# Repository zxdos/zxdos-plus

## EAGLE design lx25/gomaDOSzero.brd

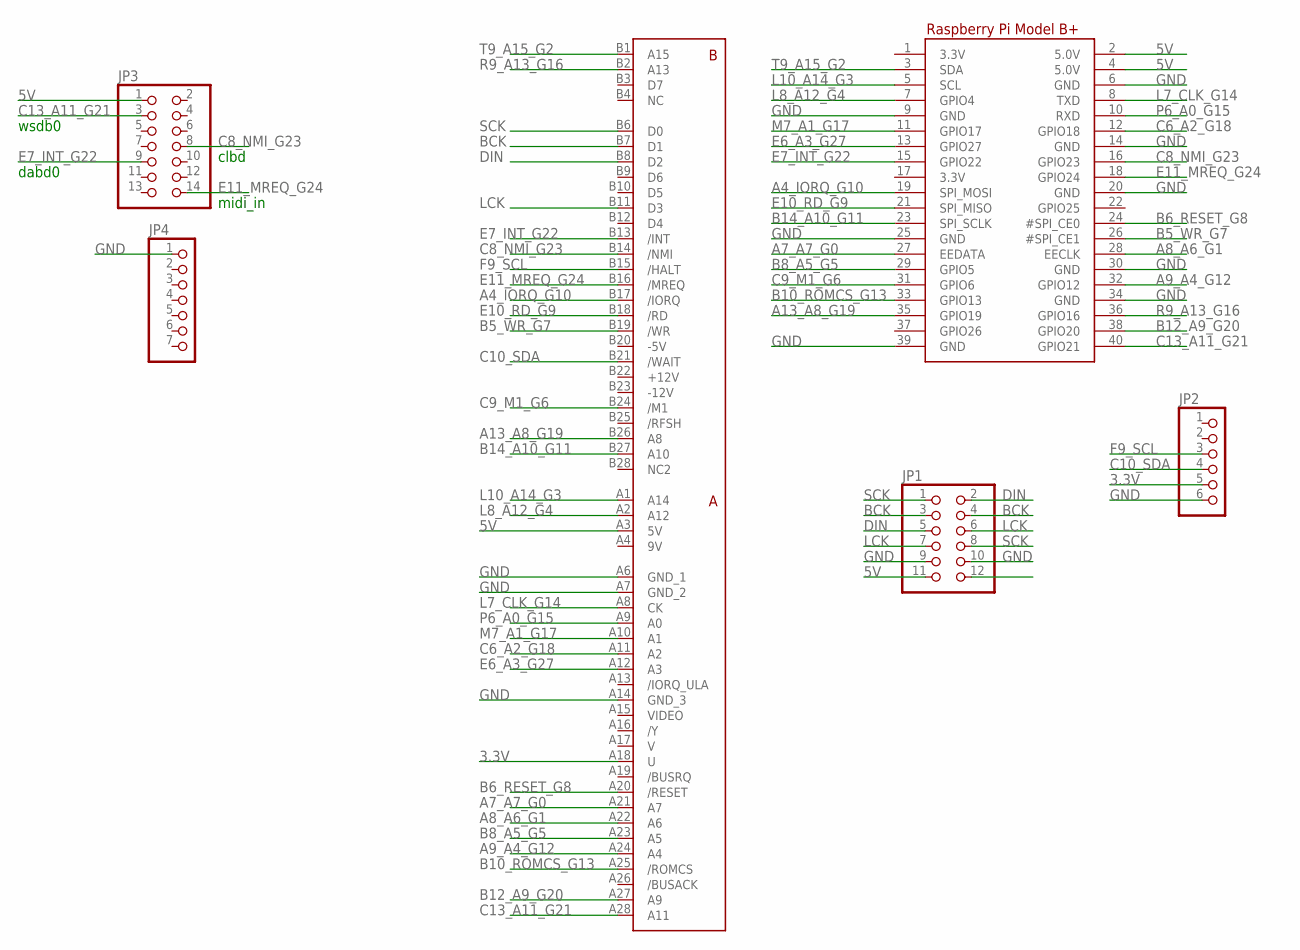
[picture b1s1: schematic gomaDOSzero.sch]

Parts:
JP1: PINHD-2X6; 2X06
JP2: PINHD-1X6/90; 1X06/90
JP3: PINHD-2X07_2.00; 2X07M
JP4: PINHD-1X07_2.00; 1X07M
RPI1: RASPBERRYPI_BPLUS_BONNETNODIM; PI_BONNET_NODIM
U$1: ZXSP_ED2X28_SPE_SOL_EDGE; 2X28_SPE2

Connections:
3.3V: JP2.5, U$1.A18 (U)
5V: JP1.11, JP1.12, JP3.1, RPI1.2 (5.0V), RPI1.4 (5.0V), U$1.A3 (5V)
9V: U$1.A4 (9V)
+12V: U$1.B22 (+12V)
-5V: U$1.B20 (-5V)
-12V: U$1.B23 (-12V)
A4_IORQ_G10: RPI1.19 (SPI_MOSI), U$1.B17 (/IORQ)
A7_A7_G0: RPI1.27 (EEDATA), U$1.A21 (A7)
A8_A6_G1: RPI1.28 (EECLK), U$1.A22 (A6)
A9_A4_G12: RPI1.32 (GPIO12), U$1.A24 (A4)
A13_A8_G19: RPI1.35 (GPIO19), U$1.B26 (A8)
B5_WR_G7: RPI1.26 (#SPI_CE1), U$1.B19 (/WR)
B6_RESET_G8: RPI1.24 (#SPI_CE0), U$1.A20 (/RESET)
B8_A5_G5: RPI1.29 (GPIO5), U$1.A23 (A5)
B10_ROMCS_G13: RPI1.33 (GPIO13), U$1.A25 (/ROMCS)
B12_A9_G20: RPI1.38 (GPIO20), U$1.A27 (A9)
B14_A10_G11: RPI1.23 (SPI_SCLK), U$1.B27 (A10)
BCK: JP1.3, JP1.4, U$1.B7 (D1)
C6_A2_G18: RPI1.12 (GPIO18), U$1.A11 (A2)
C8_NMI_G23: JP3.8, RPI1.16 (GPIO23), U$1.B14 (/NMI)
C9_M1_G6: RPI1.31 (GPIO6), U$1.B24 (/M1)
C10_SDA: JP2.4, U$1.B21 (/WAIT)
C13_A11_G21: JP3.3, RPI1.40 (GPIO21), U$1.A28 (A11)
DIN: JP1.2, JP1.5, U$1.B8 (D2)
E6_A3_G27: RPI1.13 (GPIO27), U$1.A12 (A3)
E7_INT_G22: JP3.9, RPI1.15 (GPIO22), U$1.B13 (/INT)
E10_RD_G9: RPI1.21 (SPI_MISO), U$1.B18 (/RD)
E11_MREQ_G24: JP3.14, RPI1.18 (GPIO24), U$1.B16 (/MREQ)
F9_SCL: JP2.3, U$1.B15 (/HALT)
GND: JP1.9, JP1.10, JP2.6, JP4.1, RPI1.6 (GND), RPI1.9 (GND), RPI1.14 (GND), RPI1.20 (GND), RPI1.25 (GND), RPI1.30 (GND), RPI1.34 (GND), RPI1.39 (GND), U$1.A6 (GND_1), U$1.A7 (GND_2), U$1.A14 (GND_3)
L7_CLK_G14: RPI1.8 (TXD), U$1.A8 (CK)
L8_A12_G4: RPI1.7 (GPIO4), U$1.A2 (A12)
L10_A14_G3: RPI1.5 (SCL), U$1.A1 (A14)
LCK: JP1.6, JP1.7, U$1.B11 (D3)
M7_A1_G17: RPI1.11 (GPIO17), U$1.A10 (A1)
P6_A0_G15: RPI1.10 (RXD), U$1.A9 (A0)
R9_A13_G16: RPI1.36 (GPIO16), U$1.B2 (A13)
SCK: JP1.1, JP1.8, U$1.B6 (D0)
T9_A15_G2: RPI1.3 (SDA), U$1.B1 (A15)

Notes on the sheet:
midi_in
clbd
dabd0
wsdb0

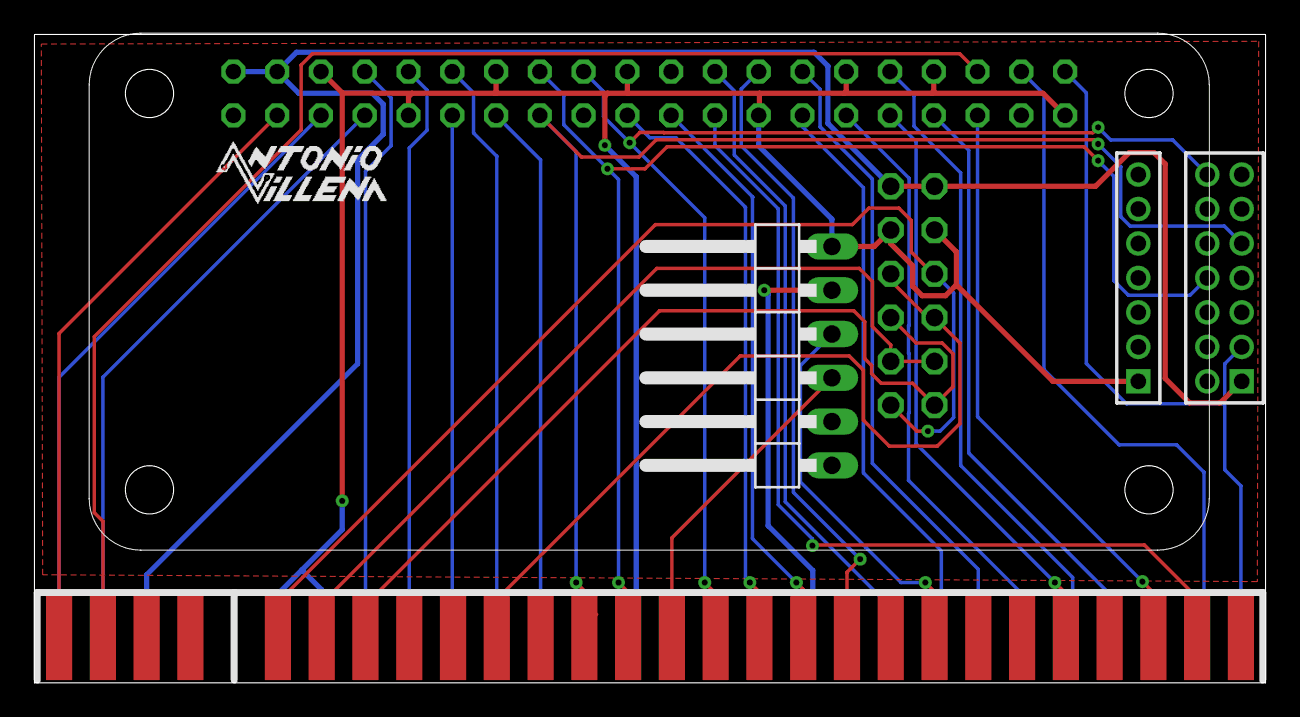
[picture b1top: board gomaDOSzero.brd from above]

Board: 2 copper layers, 71.4 x 37.6 mm, 6 parts (1 on the bottom side), 35 nets.

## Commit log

2020-07-08 basic files added
2020-08-09 Spectrum Next with working WiFi core
2020-08-09 LX25 core test
2020-08-10 Cores lx25 with joystick decoder improvement
    Cores lx25 with joystick decoder improvement
2020-08-10 Core lx25 with joystick decoder improvements
2020-08-10 Delete CORE2_test_placa_lx25.ZXD
    repetido
2020-08-15 Añado urjtag
2020-08-16 Pong AY-3-8500 core
2020-09-02 ZXNext core with support VGA666
2020-09-20 NES VGA core
2020-09-22 Full image on NES core
2020-09-29 publico ficheros PCB y gerber del addon
2020-10-02 Añado firmware original de spark2k06
2020-10-02 Añado beta del puerto edge generada por Antonio Silva
2020-10-05 Corrijo bug
2020-10-10 Arreglo tabuladores
2020-10-18 ZXNext with core launch support and monocrome mode
    Added:
    -Monocrome mode with F11 (CS+SS+Q in gomados+)
    -Launch other cores (use newcore.bas)
    -Enabled access to flash
2020-11-01 Core pong AY-3-8500 lx25 with encoder support
2020-11-08 Core pong AY-3-8500 lx25 v2.2
    Core pong AY-3-8500 lx25 with encoder and mouse support
2020-11-15 Core Atari 2600 v2.1
    Like previous lx16 version plus support for encoders, ps2 mouse and RGB output.
2020-12-19 Videopac/Odyssey2 beta1
2020-12-24 3.01.09 update
2020-12-25 ZXNext v3.01.09 hard reset issue solved
    Solved issue with hard reset not working.
2021-01-17 Videopac/Odyssey2 beta4
2021-01-30 Videopac v20210130
2021-01-31 videopac lx25
    Added BIOS videomode detection
2021-03-21 msx1.3
2021-04-04 zx48 y camputers-lynx de kypp
    Cores zx48 y camputers-lynx de kypp con VGA, joystick y hardreset, el zx48 también incluye salida i2s
2021-04-24 chip-8 zxdos+ lx25
    chip-8 zxdos+ lx25
2021-05-15 Videopac/Oddyssey2 for ZXDOS+
    Solved volley bug
2021-05-16 chip-8 with RGB support
    Added RGB support and zxuno reset keys
2021-05-23 chip8 VGA/RGB(NTSC)
    Changed pixel size
2021-06-06 joydecoder for zxdos+ boards md joysticks
    Joydecoder for zxdos+ boards md joysticks
2021-06-12 ZXNext 3.1.10
    New version 3.1.9 with improved MD joystick.
    New version 3.1.10.
    Both versions for new ZXDOS+ with 1M16bits and old ones with 2M16bits.
    Version 1x16 is compatible with both ZDOS+ versions
2021-06-12 SPECTRUM MD joystick
2021-11-01 zx81 port from Mister
2022-02-17 Añado core pc
2022-02-17 paso a zip y añado bios
2022-06-05 ZX81 release 20220604 bug solve
2024-01-16 zxnext 3.02.01

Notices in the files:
parts and their libraries:
microbuilder: This work is placed in the public domain, and may be freely used for commercial and non-commercial work with the following conditions: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
